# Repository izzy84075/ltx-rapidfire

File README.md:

LTX-RapidFire
=============

DIY LTX RapidFire! Custom attachments compatible with the Lazer Tag Phoenix LTX!

This project has everything you need to make your own weapon attachments for the Lazer Tag Phoenix LTX with just a bit of soldering skill and minor reading abilities. Other kinds of attachments could be made with this code if you know what you're doing, but as-provided, it is designed for weapon-like attachments only.

Pretty much everything is documented now!

This code is provided under the GPL v2 license.

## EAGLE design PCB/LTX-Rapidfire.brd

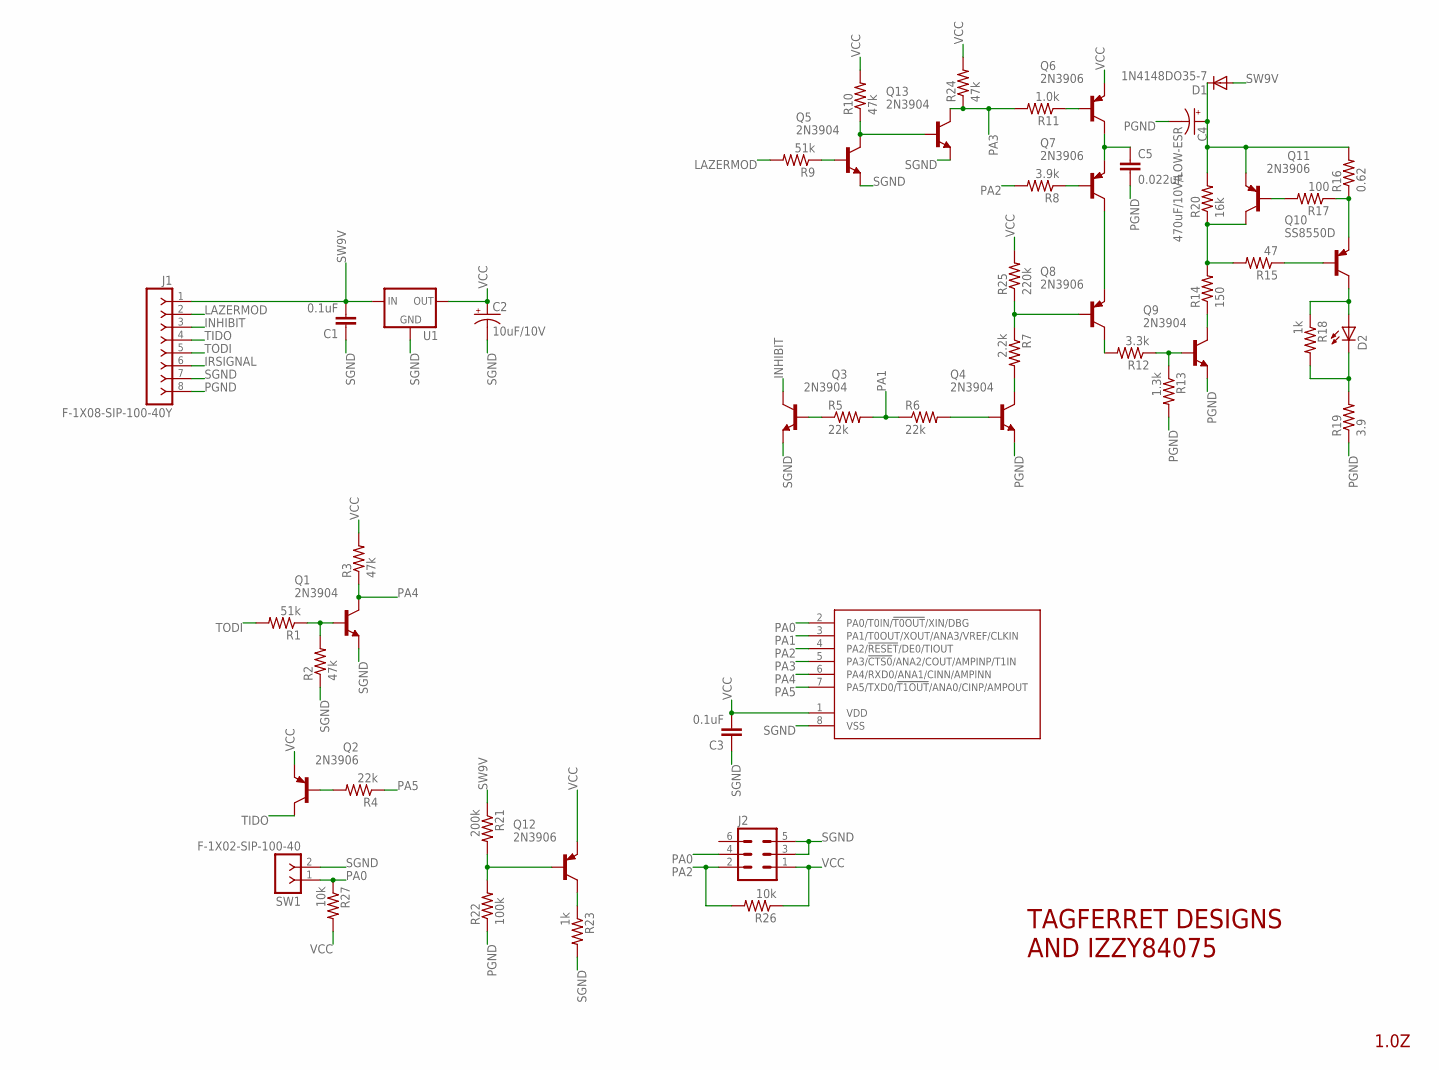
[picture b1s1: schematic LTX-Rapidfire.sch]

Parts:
C1, C3: 0.1uF; C025-025X050
C2: 10uF/10V; E2-4
C4: 470uF/10V/LOW-ESR; E3,5-8
C5: 0.022uF; C025-025X050
D1: 1N4148DO35-7; DO35-7
D2: LED5MM
J1: F-1X08-SIP-100-40Y; SIP-100-08-40Y
J2: MA03-2
Q1, Q3, Q4, Q5, Q9, Q13: 2N3904; TO92
Q2, Q6, Q7, Q8, Q11, Q12: 2N3906; TO92
Q10: SS8550D; TO92
R1, R9: 51k; 0204/7
R2, R3, R10, R24: 47k; 0204V
R4, R5, R6: 22k; 0204/7
R7: 2.2k; 0204/7
R8: 3.9k; 0204/7
R11: 1.0k; 0204/7
R12: 3.3k; 0204/7
R13: 1.3k; 0204V
R14: 150; 0204/7
R15: 47; 0204/7
R16: 0.62; 0204/7
R17: 100; 0204V
R18: 1k; 0204V
R19: 3.9; 0207/10
R20: 16k; 0204V
R21: 200k; 0204/7
R22: 100k; 0204V
R23: 1k; 0204/7
R25: 220k; 0204V
R26, R27: 10k; 0204V
SW1: F-1X02-SIP-100-40; SIP-100-02-40
U1: 78LXX
U2: Z8F082ADIL-8; DIL8

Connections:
INHIBIT: J1.3, Q3.1 (C)
IRSIGNAL: J1.6
LAZERMOD: J1.2, R9.2
unnamed: Q11.2 (B), R17.2
unnamed: C4.+, D1.C, Q11.3 (E), R16.2, R20.2
unnamed: Q10.3 (E), R16.1, R17.1
unnamed: Q11.1 (C), R14.2, R15.2, R20.1
unnamed: Q10.2 (B), R15.1
unnamed: Q9.1 (C), R14.1
unnamed: D2.K (C), R18.2, R19.2
unnamed: D2.A, Q10.1 (C), R18.1
unnamed: Q9.2 (B), R12.1, R13.1
unnamed: Q8.1 (C), R12.2
unnamed: Q7.1 (C), Q8.3 (E)
unnamed: Q8.2 (B), R7.1, R25.1
unnamed: Q7.2 (B), R8.1
unnamed: Q4.1 (C), R7.2
unnamed: C5.1, Q6.1 (C), Q7.3 (E)
unnamed: Q4.2 (B), R6.2
unnamed: Q12.1 (C), R23.1
unnamed: Q3.2 (B), R5.1
unnamed: Q6.2 (B), R11.1
unnamed: Q12.2 (B), R21.2, R22.2
unnamed: Q5.1 (C), Q13.2 (B), R10.1
unnamed: Q5.2 (B), R9.1
unnamed: Q1.2 (B), R1.1, R2.2
unnamed: Q2.2 (B), R4.2
PA0: J2.4, R27.1, SW1.1, U2.2 (PA0/T0IN/!T0OUT!/XIN/DBG)
PA1: R5.2, R6.1, U2.3 (PA1/T0OUT/XOUT/ANA3/VREF/CLKIN)
PA2: J2.2, R8.2, R26.2, U2.4 (PA2/!RESET!/DE0/TIOUT)
PA3: Q13.1 (C), R11.2, R24.1, U2.5 (PA3/!CTS0!/ANA2/COUT/AMPINP/T1IN)
PA4: Q1.1 (C), R3.1, U2.6 (PA4/RXD0/ANA1/CINN/AMPINN)
PA5: R4.1, U2.7 (PA5/TXD0/!T1OUT!/ANA0/CINP/AMPOUT)
PGND: C4.-, C5.2, J1.8, Q4.3 (E), Q9.3 (E), R13.2, R19.1, R22.1
SGND: C1.1, C2.-, C3.1, J1.7, J2.3, J2.5, Q1.3 (E), Q3.3 (E), Q5.3 (E), Q13.3 (E), R2.1, R23.2, SW1.2, U1.GND, U2.8 (VSS)
SW9V: C1.2, D1.A, J1.1, R21.1, U1.IN
TIDO: J1.4, Q2.1 (C)
TODI: J1.5, R1.2
VCC: C2.+, C3.2, J2.1, Q2.3 (E), Q6.3 (E), Q12.3 (E), R3.2, R10.2, R24.2, R25.2, R26.1, R27.2, U1.OUT, U2.1 (VDD)

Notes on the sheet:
TAGFERRET DESIGNS AND IZZY84075
1.0Z

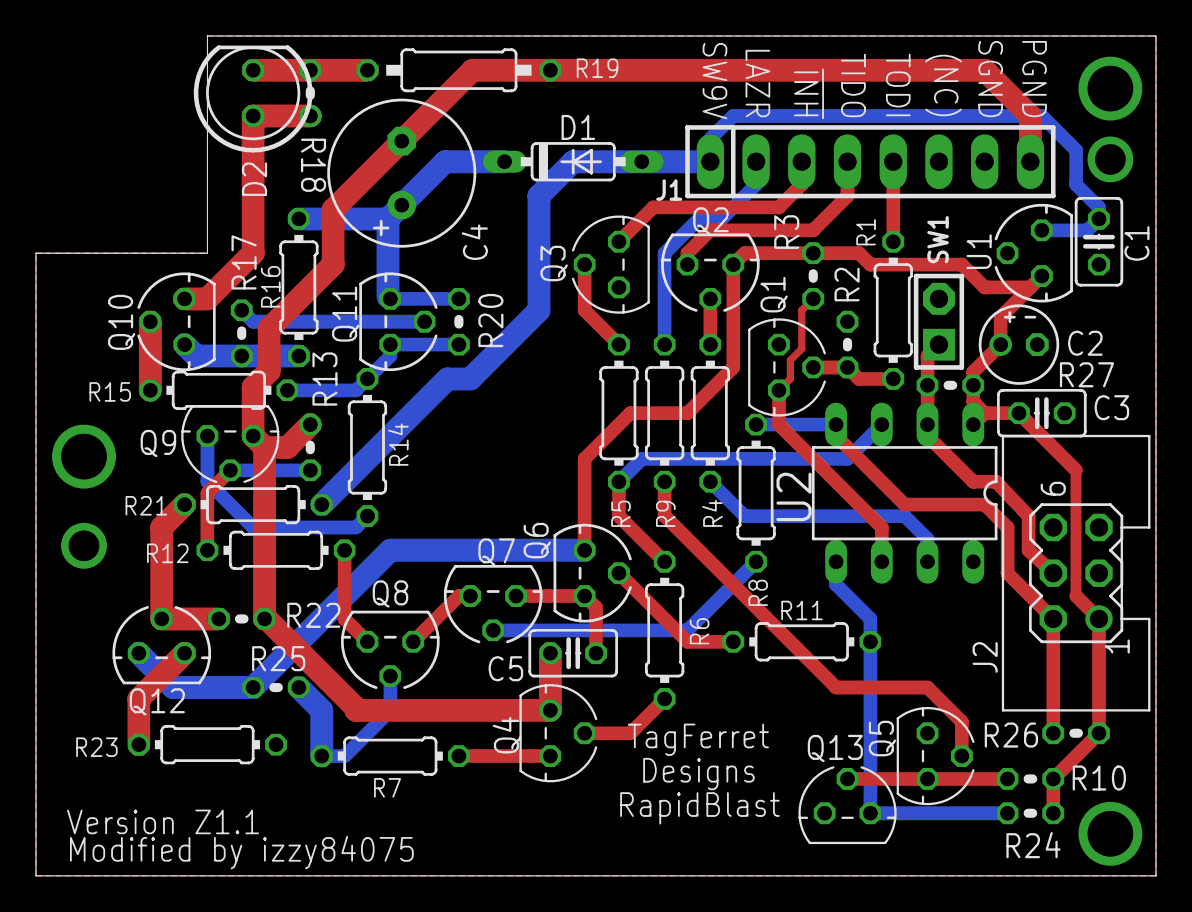
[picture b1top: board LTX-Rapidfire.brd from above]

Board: 2 copper layers, 62.2 x 46.7 mm, 52 parts (0 on the bottom side), 38 nets.

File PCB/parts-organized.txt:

Type		Value		Package			Part						Quantity	Mouser #

Cap			0.1uF						C1,C3						2			594-K104K15X7RF5UH5
Cap			10uF/10V					C2							1			581-TAP106K010CCS
Cap			470uF/10V/LOW-ESR			C4							1			140-RXK471M1ABK0815P
Cap			0.022uF						C5							1			594-K223K15X7RF53L2

Diode					DO-35			D1							1			583-1N4148-T

LED			TSAL-6100					D2							1			782-TSAL6100

Header		2x3 Male, Shrouded			J2							1			517-30306-6002HB

Transistor	2N3904						Q1,Q3,Q4,Q5,Q9,Q13			6			610-2N3904
Transistor	2N3906						Q2,Q6,Q7,Q8,Q11,Q12			6			610-2N3906
Transistor	SS8550D						Q10							1			512-SS8550DTA

Resistor	0.62						R16							1			660-MOX1CT52RR62J
Resistor	3.9							R19							1			660-MOSX1CT52R3R9J
Resistor	47							R15							1			660-MF1/4DCT52R47R0F
Resistor	100							R17							1			660-MF1/4DC1000F
Resistor	150							R14							1			660-MF1/4DCT52A1500F
Resistor	1K							R11,R18,R23					3			660-MF1/4DC1001F
Resistor	1.3K						R13							1			660-MF1/4DC1301F
Resistor	2.2K						R7							1			660-MF1/4DCT52R2201F
Resistor	3.3K						R12							1			660-MF1/4DCT52R3301F
Resistor	3.9K						R8							1			660-MF1/4DCT52R3901F
Resistor	10K							R26,R27						2			660-MF1/4DCT52A1002F
Resistor	16K							R20							1			660-MF1/4DCT52R1602F
Resistor	22K							R4,R5,R6					3			660-MF1/4DCT52R2202F
Resistor	47K							R2,R3,R10,R24				4			660-MF1/4DCT52R4702F
Resistor	51K							R1,R9						2			660-MF1/4DCT52R5102F
Resistor	100K						R22							1			660-MF1/4DCT52A1003F
Resistor	200K						R21							1			660-MS1/4DCT52R2003
Resistor	220K						R25							1			660-MF1/4DCT52R2203F

VREG		3.3V		TO-92			U1							1			511-LE33CZ-TR

MCU			Z8F082A		DIL8			U2							1			692-Z8F082APB020SG

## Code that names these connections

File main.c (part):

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void init_cpu(void) {
	DI();
	
	//PA0: RELOAD/DBG. Input, external 10k pullup.
	//PA1: INHIBIT. Output.
	//PA2: 38KHz. T1OUT, output.
	//PA3: LAZERMOD. Input.
	//PA4: RXD. UART, input.
	//PA5: TXD. UART, output.
	
	//Set up Port A.
	PADD = 0x19;	//00011001
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
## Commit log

2013-12-14 Whoops. Didn't have this in Git before... But anyways! This is the code for a DIY LTX-compatible RapidFire(Or whatever other weapon you want) attachment. It works, though there are some enhancements 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
2013-12-14 And speaking of enhancements, let's make it so that we can choose whether or not to allow reloading the attachment mid-clip. It won't reload when the clip's already full, but it will if you fire a si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
2013-12-16 Add license information before making public.
2013-12-16 Add a bit more to the README.md.
2013-12-17 Add a ton of comments, clean up a bunch.
    Added comments to almost everything, made more of the weapon details
    configurable from the defines at the top of the file, and fixed up a few
    little things that no longer needed to be where they were.
2013-12-17 Add a few more comments and tweak the Sniper
    Made the provided Sniper profile act somewhat like a sniper.
2013-12-17 Rename WEAPONTYPE to WEAPONPROFILE
    Should reduce confusion between WEAPONTYPE and BARRELTYPE. Also makes a
    bit more sense, with how it's supposed to be used.
2013-12-17 Mark that DoubleTaps are crazy.
    As of yet, I don't fully understand DoubleTaps myself. If anybody wants to experiment with how they work, and support them properly, submit a pull request with your code and I'll look at it.
2013-12-19 Add .h files
    Split out the function prototypes, global variables, and configuration
    data to their own files, as should have been done long ago. This is
    actually starting to look like a decent project!
2013-12-19 Add some instructions.
    Incomplete as of yet, but I still don't have the PCB schematics or parts
    list to finish the rest of it.
2013-12-19 Take out the temporary TX buffer.
    Also tried updating the "factory test" mode bit, but it doesn't seem to
    work anymore. Not sure why.
2014-05-31 Move code into a subfolder in preparation for PCB files.
2014-05-31 Older PCB files. NOBODY ORDER THESE! THEY WILL NOT WORK WITH THE CURRENT CODE! THEY ARE FOR A DIFFERENT PROCESSOR!
2014-05-31 Whoops. Accidentally moved the readme.
2014-05-31 Starting in on current schematic.
2014-05-31 A (hopefully) complete schematic...
2014-05-31 Whoops. Missed some bits. /Now/ it's complete.
2014-06-05 First pass of PCB layout is complete.
    Cleanup is in progress, but they should technically work as-is. Labels
    are going to be impossible to see, though.
2014-06-05 Let's rotate the board so that it fits on my screen better, now that I'm not converting measurements between ExpressPCB and Eagle.
2014-06-05 Labels and silkscreen!
2014-06-05 I suppose making it pass DRC would be good...
2014-06-05 Tweaking for OSHPark rendering.
2014-06-15 Parts list!
2014-06-15 And converted to Mouser's BOM Import format.
2014-06-15 Add a .gitignore so we don't drag around more unnecessary binaries.
2014-06-15 Add some "starter" firmware.
2014-06-15 Add some basic instructions. I should come back and add more details(And the entire Firmware file...), but for now...
2014-06-15 Update the project files to current.
2014-07-17 Programming instructions for the "starter" firmware file.
2014-10-06 A resistor got missed! Whoops. Put that back in...
2014-10-06 Update the partslists to add in that missing resistor.
2014-10-22 Replace R19 out so you can fit a 1/2W resistor in.
2014-10-22 Replace the special order capacitor with a normally stocked one.
2014-12-10 Update the readme.
2014-12-11 Update Mouser BOM, to meet their new standard...
2014-12-11 Swap for a different capacitor.
2014-12-22 Update PCB purchase link.
2014-12-22 Tweak instructions.
2014-12-22 Update readme.
2015-07-24 Add DoubleTap support and documentation, and a couple more configuration options to really take advantage of it!
2015-07-25 Discovering more bits of minutiae about the LTX.
2015-08-17 An extra #endif snuck into config.h, and an error in the comments for DoubleTaps were pointed out to me. Fix those!

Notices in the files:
main.c:
Copyright (C) 2013  Ryan L. "Izzy84075" Bales
This program is free software; you can redistribute it and/or modify
it under the terms of the GNU General Public License as published by
the Free Software Foundation; either version 2 of the License, or
(at your option) any later version.
parts and their libraries:
con-headers-jp: Copyright (C) 2008, Bob Starr
